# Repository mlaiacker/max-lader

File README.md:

# max-lader
DIY Battery Charger, 12V Input, 0-25V Output, 5.5A, using AVR
With these components the charger is limited to about 120W and maximum input voltage of about 15V

See also: 
http://mlaiacker.no-ip.org/Modellbau/AVR-Lader/
## Charging
Type | Cells
----|----
LiPo | 1-6
LiFe | 1-7
NiMh/NiCa| 1-16
PB | 1-6 (2-12V)
Programmable Power Supply | 0-25V 0-5.5A
## Characteristics
Parameter | Value
----|----
Input Voltage | 11-15V
Output Voltage | 0-25V
Voltage Resolution | 0-13V 14mV , >13V 27mV 
Output Current | 0-5.5A
Current Resolution | 6.6mA
Power | up to 125W
PWM Switching Frequency | 31.25kHz (16MHz/512)
PWM Resolution | 9 Bits
Efficiency | up to 89%
## Images
MAX-Lader with big heat sink which not really necessary.<br>

<br>
The charger without the LCD and enclosure<br>

## Electronics
The electronics are mostly thru hole and optimized for home production double sided PCB. The output voltage and current is regulated using a buck/boost converter which is software controlled by the AVR. The main coil is self made which is easy. The electronics fit nicely into the enclosure but the space is limited that is why there is no balancer electronics included. The LCD should be 2x16 (HD44780) characters with 14 or 16 pins on the lower left corner. The MOSFETs and diode have to be mounted electrical isolated from the enclosure/heat sink. Mounting the Mosfets behind the output caps is a bit tricky. The output caps have to be LowESR types. The resistors for the voltage dividers for the output and current should be 0.1% types to ensure the correct voltages when charging LIPOs. The input is reverse voltage protected but the output is not. Output caps will blow when a battery is connected the wrong way.

Using bigger or more MOSFETs and bigger coil and smaller shunt resistors should enable more output power. The maximum input voltage is limited by the ICL7667 max. voltage and max. GS-Voltage of the P-Channel Mosfet (IRF4905)
## Software
The Software is heavily optimized for size to fit in the ATmega8 that was originally used. It can be build for the ATmega8 or for the newer ATmega168. Using the ATmega168 will enable some more functions like display of data from a Robbe Top Lipo Equalizer 6S when connected to the serial port. The menu is in German but very easy: <br>
Step 1: Select battery type<br>
Step 2: Set Cell count<br>
Step 3: Set Current<br>
Step 4: Connect battery (charging will start automatically when a battery is connected) <br>
## Bootloader
There is no ISP connector on the PCB so you have to program the bootloader before installing the AVR to the charger. The bootloader is activated when the middle button is pressed during power up. The program can be loaded using the serial interface using stk500v1 protocol with avrdude.

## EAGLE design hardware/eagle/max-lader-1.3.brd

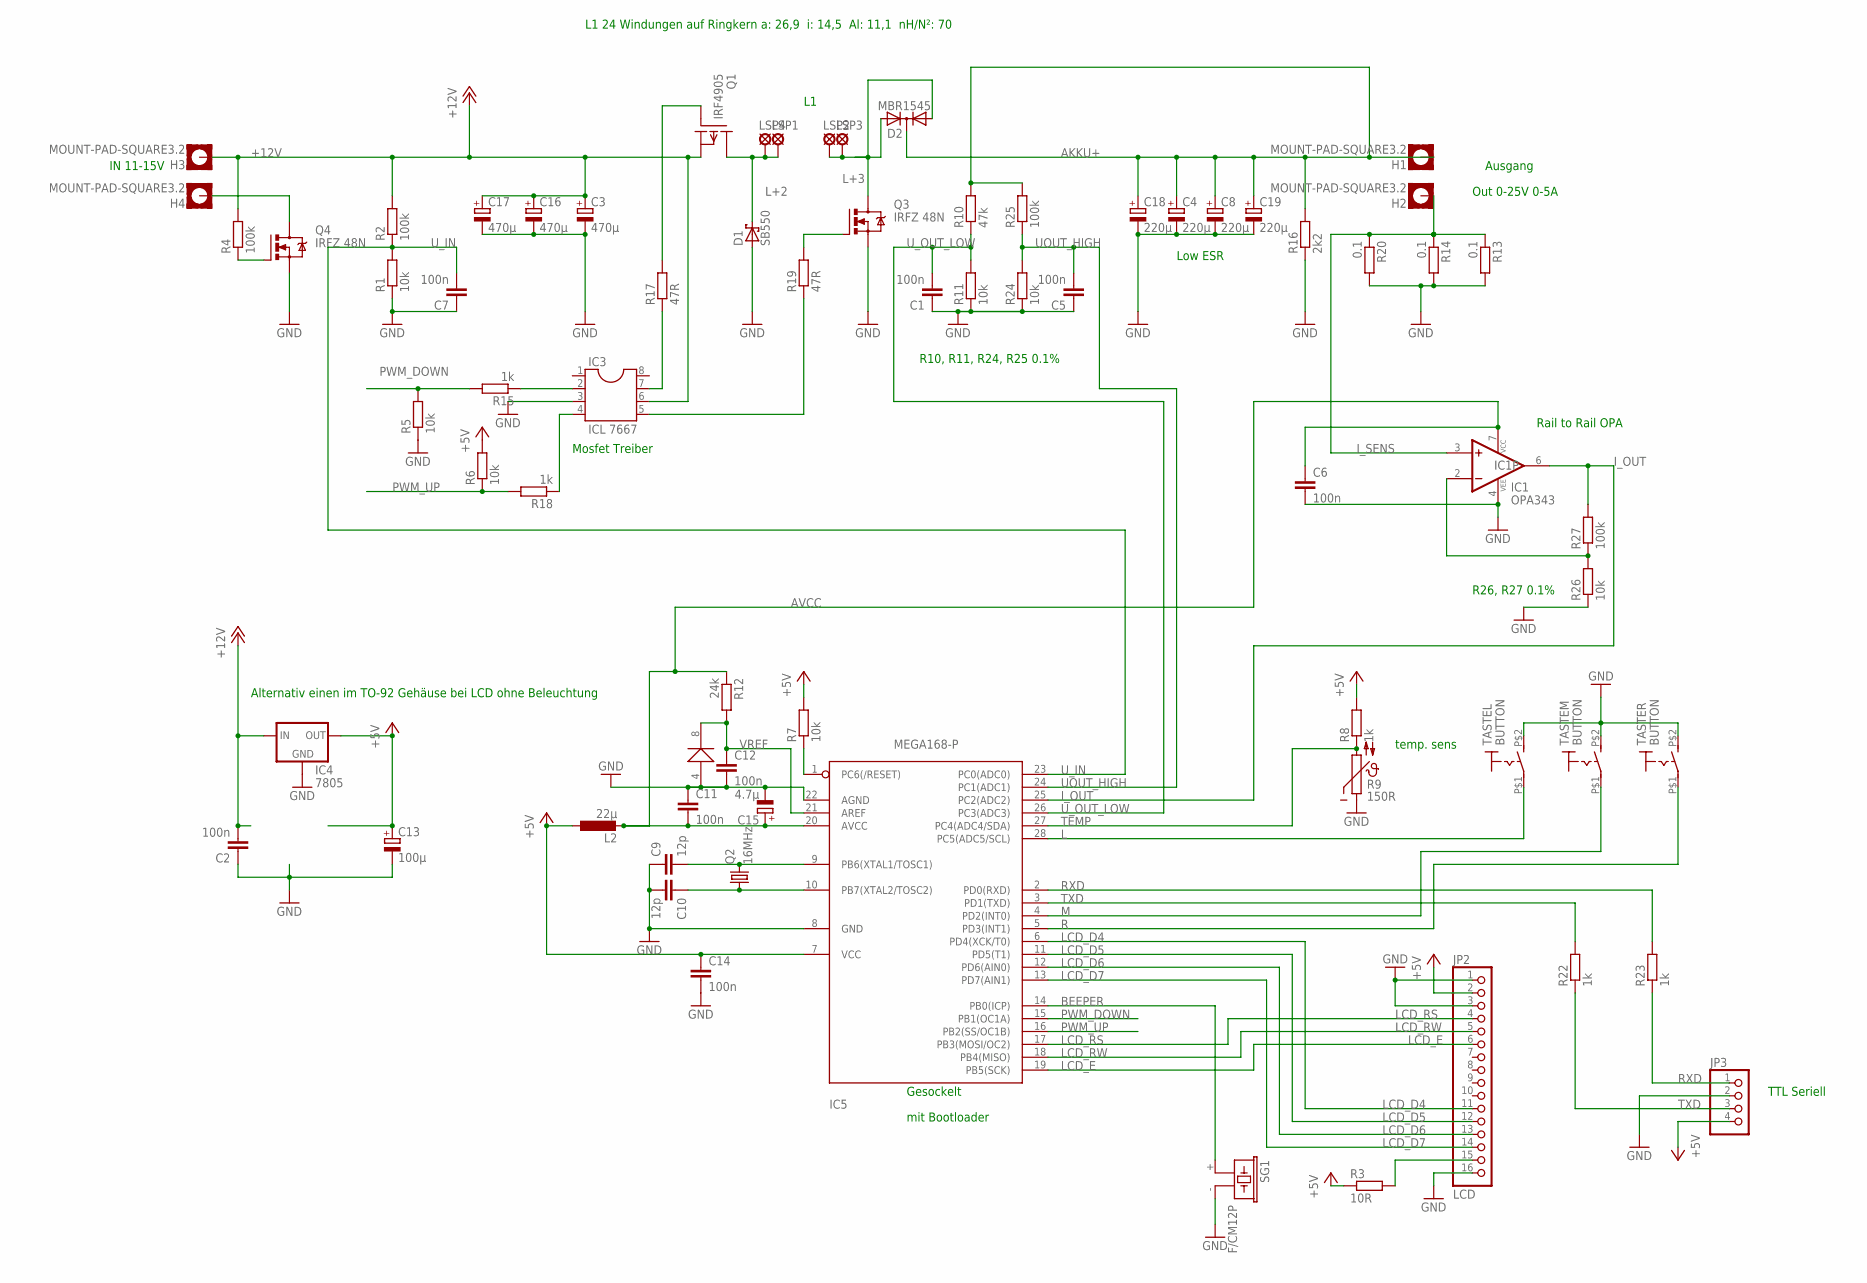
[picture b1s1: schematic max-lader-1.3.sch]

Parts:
C1, C5, C6, C12, C14: 100n; C050-024X044
C2, C7, C11: 100n; C050-025X075
C3, C16, C17: 470µ; E3,5-8
C4, C8, C18, C19: 220µ; E3,5-8
C9, C10: 12p; C050-024X044
C13: 100µ; E3,5-8
C15: 4.7µ; E2-4
D1: SB550; DO201T15
D2: MBR1545; TO220ABS
H1, H2, H3, H4: MOUNT-PAD-SQUARE3.2; 3,2-PAD-SQUARE
IC1: OPA343; SO08
IC2: LM385-2.5; SO08
IC3: ICL 7667; DIL08
IC4: 7805; 78XXL
IC5: MEGA168-P; DIL28-3
JP2: LCD; 1X16
JP3: PINHD-1X4; 1X04
L2: 22µ; 0207/12
LSP1, LSP2, LSP3, LSP4: SE13
Q1: IRF4905; TO220V
Q2: 16MHz; HC49/S
Q3, Q4: IRFZ 48N; TO220BV
R1, R11, R24, R26: 10k; 0207/10
R2, R25, R27: 100k; 0207/10
R3: 10R; 0207/10
R4: 100k; 0204/7
R5, R6, R7: 10k; R0805
R8, R15, R18, R22, R23: 1k; R0805
R9: 150R; P642
R10: 47k; 0207/10
R12: 24k; 0207/10
R13, R14, R20: 0.1; P0613/15
R16: 2k2; 0207/2V
R17, R19: 47R; 0207/10
SG1: F/CM12P
TASTEL: BUTTON; BUT
TASTEM: BUTTON; BUT
TASTER: BUTTON; BUT

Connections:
+5V: C13.+, C14.1, IC4.OUT, IC5.7 (VCC), JP2.2, JP3.4, L2.1, R3.1, R6.2, R7.2, R8.2
+12V: C2.2, C3.+, C16.+, C17.+, H3.B3,2, IC3.6, IC4.IN, Q1.3 (S), R2.2, R4.2
AKKU+: C4.+, C8.+, C18.+, C19.+, D2.C, H1.B3,2, R10.2, R16.2, R25.2
AVCC: C6.1, C11.2, C15.+, IC1.7 (VCC), IC5.20 (AVCC), L2.2, R12.1
BAT-: H4.B3,2, Q4.D
BEEPER: IC5.14 (PB0(ICP)), SG1.+ (1)
BOOST_CTRL: IC3.5, R19.1
BOOST_GATE: Q3.G, R19.2
BUCK_CTRL: IC3.7, R17.1
BUCK_GATE: Q1.1 (G), R17.2
GND: C1.1, C2.1, C3.-, C4.-, C5.1, C6.2, C7.1, C8.-, C9.1, C10.2, C11.1, C12.2, C13.-, C14.2, C15.-, C16.-, C17.-, C18.-, C19.-, D1.A, IC1.4 (VEE), IC2.4 (ANODE), IC3.3, IC4.GND, IC5.8 (GND), IC5.22 (AGND), JP2.1, JP2.3, JP2.16, JP3.2, Q3.S, Q4.S, R1.1, R5.1, R9.1, R11.1, R13.2, R14.2, R16.1, R20.2, R24.1, R26.1, SG1.- (2), TASTEL.P$2 (S), TASTEM.P$2 (S), TASTER.P$2 (S)
INPUT_GATE: Q4.G, R4.1
I_OUT: IC1.6 (OUT), IC5.25 (PC2(ADC2)), R27.2
I_SENS: H2.B3,2, IC1.3 (+IN), R13.1, R14.1, R20.1
L: IC5.28 (PC5(ADC5/SCL)), TASTEL.P$1
L+2: D1.C, LSP1.MP, LSP4.MP, Q1.2 (D)
L+3: D2.A1, D2.A2, LSP2.MP, LSP3.MP, Q3.D
LCD_D4: IC5.6 (PD4(XCK/T0)), JP2.11
LCD_D5: IC5.11 (PD5(T1)), JP2.12
LCD_D6: IC5.12 (PD6(AIN0)), JP2.13
LCD_D7: IC5.13 (PD7(AIN1)), JP2.14
LCD_E: IC5.19 (PB5(SCK)), JP2.6
LCD_RS: IC5.17 (PB3(MOSI/OC2)), JP2.4
LCD_RW: IC5.18 (PB4(MISO)), JP2.5
M: IC5.4 (PD2(INT0)), TASTEM.P$1
unnamed: IC3.4, R18.1
unnamed: IC5.1 (PC6(/RESET)), R7.1
unnamed: IC3.2, R15.1
unnamed: C9.2, IC5.9 (PB6(XTAL1/TOSC1)), Q2.2
unnamed: C10.1, IC5.10 (PB7(XTAL2/TOSC2)), Q2.1
unnamed: JP2.15, R3.2
unnamed: IC1.2 (-IN), R26.2, R27.1
PWM_DOWN: IC5.15 (PB1(OC1A)), R5.2, R15.2
PWM_UP: IC5.16 (PB2(SS/OC1B)), R6.1, R18.2
R: IC5.5 (PD3(INT1)), TASTER.P$1
RXD: IC5.2 (PD0(RXD)), R23.2
RXD_OUT: JP3.1, R23.1
TEMP: IC5.27 (PC4(ADC4/SDA)), R8.1, R9.2
TXD: IC5.3 (PD1(TXD)), R22.2
TXD_OUT: JP3.3, R22.1
UOUT_HIGH: C5.2, IC5.24 (PC1(ADC1)), R24.2, R25.1
U_IN: C7.2, IC5.23 (PC0(ADC0)), R1.2, R2.1
U_OUT_LOW: C1.2, IC5.26 (PC3(ADC3)), R10.1, R11.2
VREF: C12.1, IC2.8 (CATODE), IC5.21 (AREF), R12.2

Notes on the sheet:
Ausgang
temp. sens
Rail to Rail OPA
Gesockelt
mit Bootloader
TTL Seriell
Mosfet Treiber
IN 11-15V
Out 0-25V 0-5A
R10, R11, R24, R25 0.1%
R26, R27 0.1%
Low ESR
L1 24 Windungen auf Ringkern a: 26,9 i: 14,5 Al: 11,1 nH/N²: 70
Alternativ einen im TO-92 Gehäuse bei LCD ohne Beleuchtung

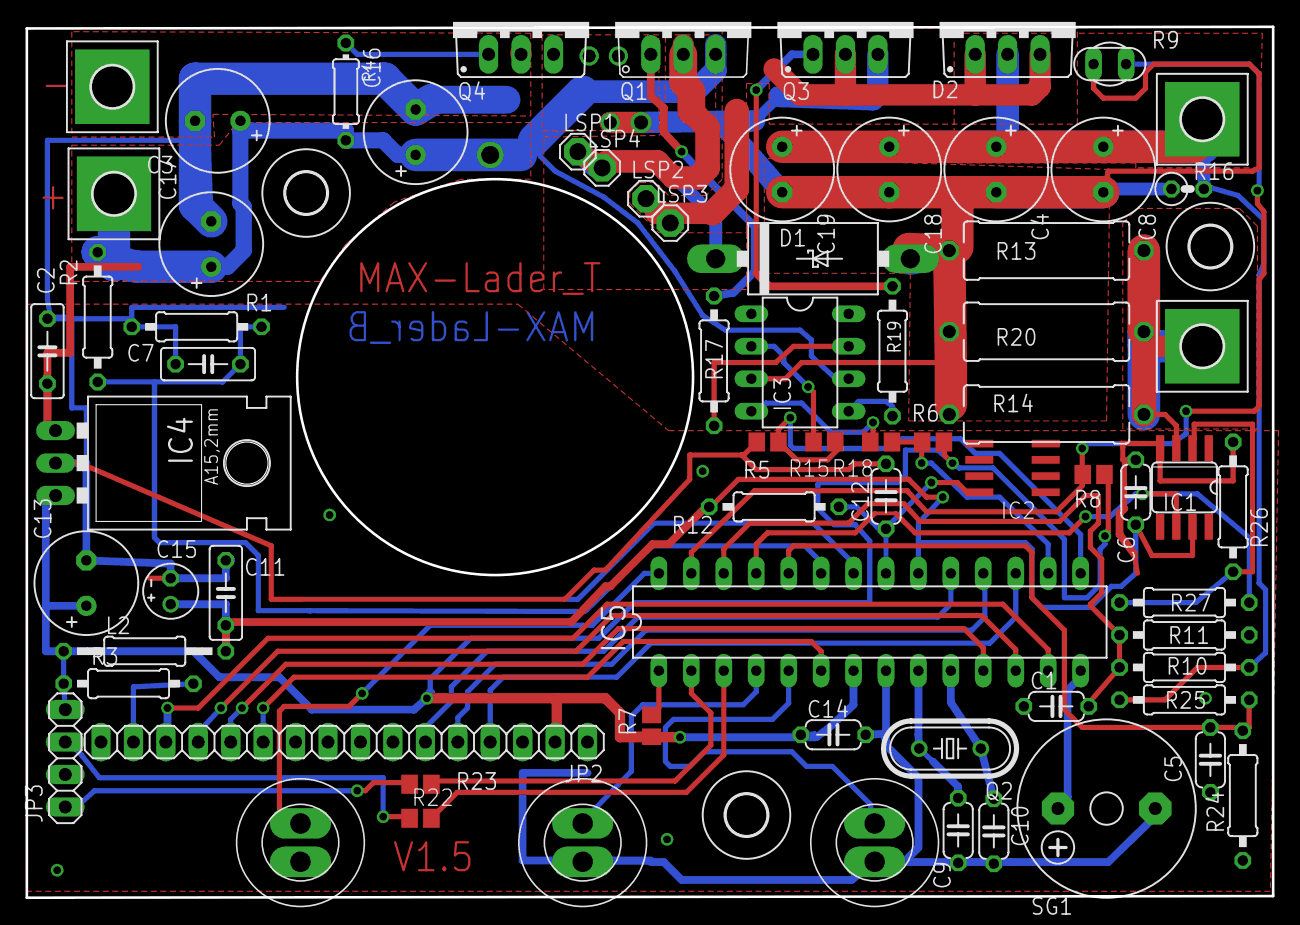
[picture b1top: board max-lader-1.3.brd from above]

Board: 2 copper layers, 97.6 x 68.2 mm, 74 parts (0 on the bottom side), 44 nets.

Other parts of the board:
U$2, U$3, U$4: 3,2

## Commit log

2015-03-21 gitignore
2015-03-21 initial avr software
2015-03-21 images for readme.md
2015-03-21 added schematics for hw version 1.3
2015-03-21 hex files and doc
2016-04-03 chages to compile with newer avr.gcc
    avr-gcc (AVR_8_bit_GNU_Toolchain_3.5.0_1662) 4.9.2
2019-11-13 makefile update for bootloader
2019-11-13 added progam_all target to flash bootloader and main programm at once and fixed size print
2019-11-13 fixed size print in Makefile
2019-11-13 bootloader added lcd support
2019-11-13 added LiHv (4,3V cell) support, show end voltage when setting up cell count, show input voltage on start menu, moved to version 1.6
2019-11-13 eagle files
2019-11-15 changed pwm control algorithm to PID works better, added "oscilloscope" function for debug of PWM with matlab plotting script
2019-11-16 atmega8 compatible, bootloader added auto start of main program after firmware upload
2020-03-17 added hyteresis to pwm control, tested on atmega168, fixed debug trigger bug
2020-03-29 optimized for atmega8 so it will fit
2020-04-10 changed charger logic a bit and code style cleanup
2020-04-10 removed pwm control debug feature for now
2020-04-11 code cleanup, changed baudrate to 38400 and added auto reboor tor firmware update with mega168 cahnged control algorithm
2021-04-13 layout version 1.5 with 1k protection resistors for icl7667 failure on overvoltage, it will kill the atmega168 without
